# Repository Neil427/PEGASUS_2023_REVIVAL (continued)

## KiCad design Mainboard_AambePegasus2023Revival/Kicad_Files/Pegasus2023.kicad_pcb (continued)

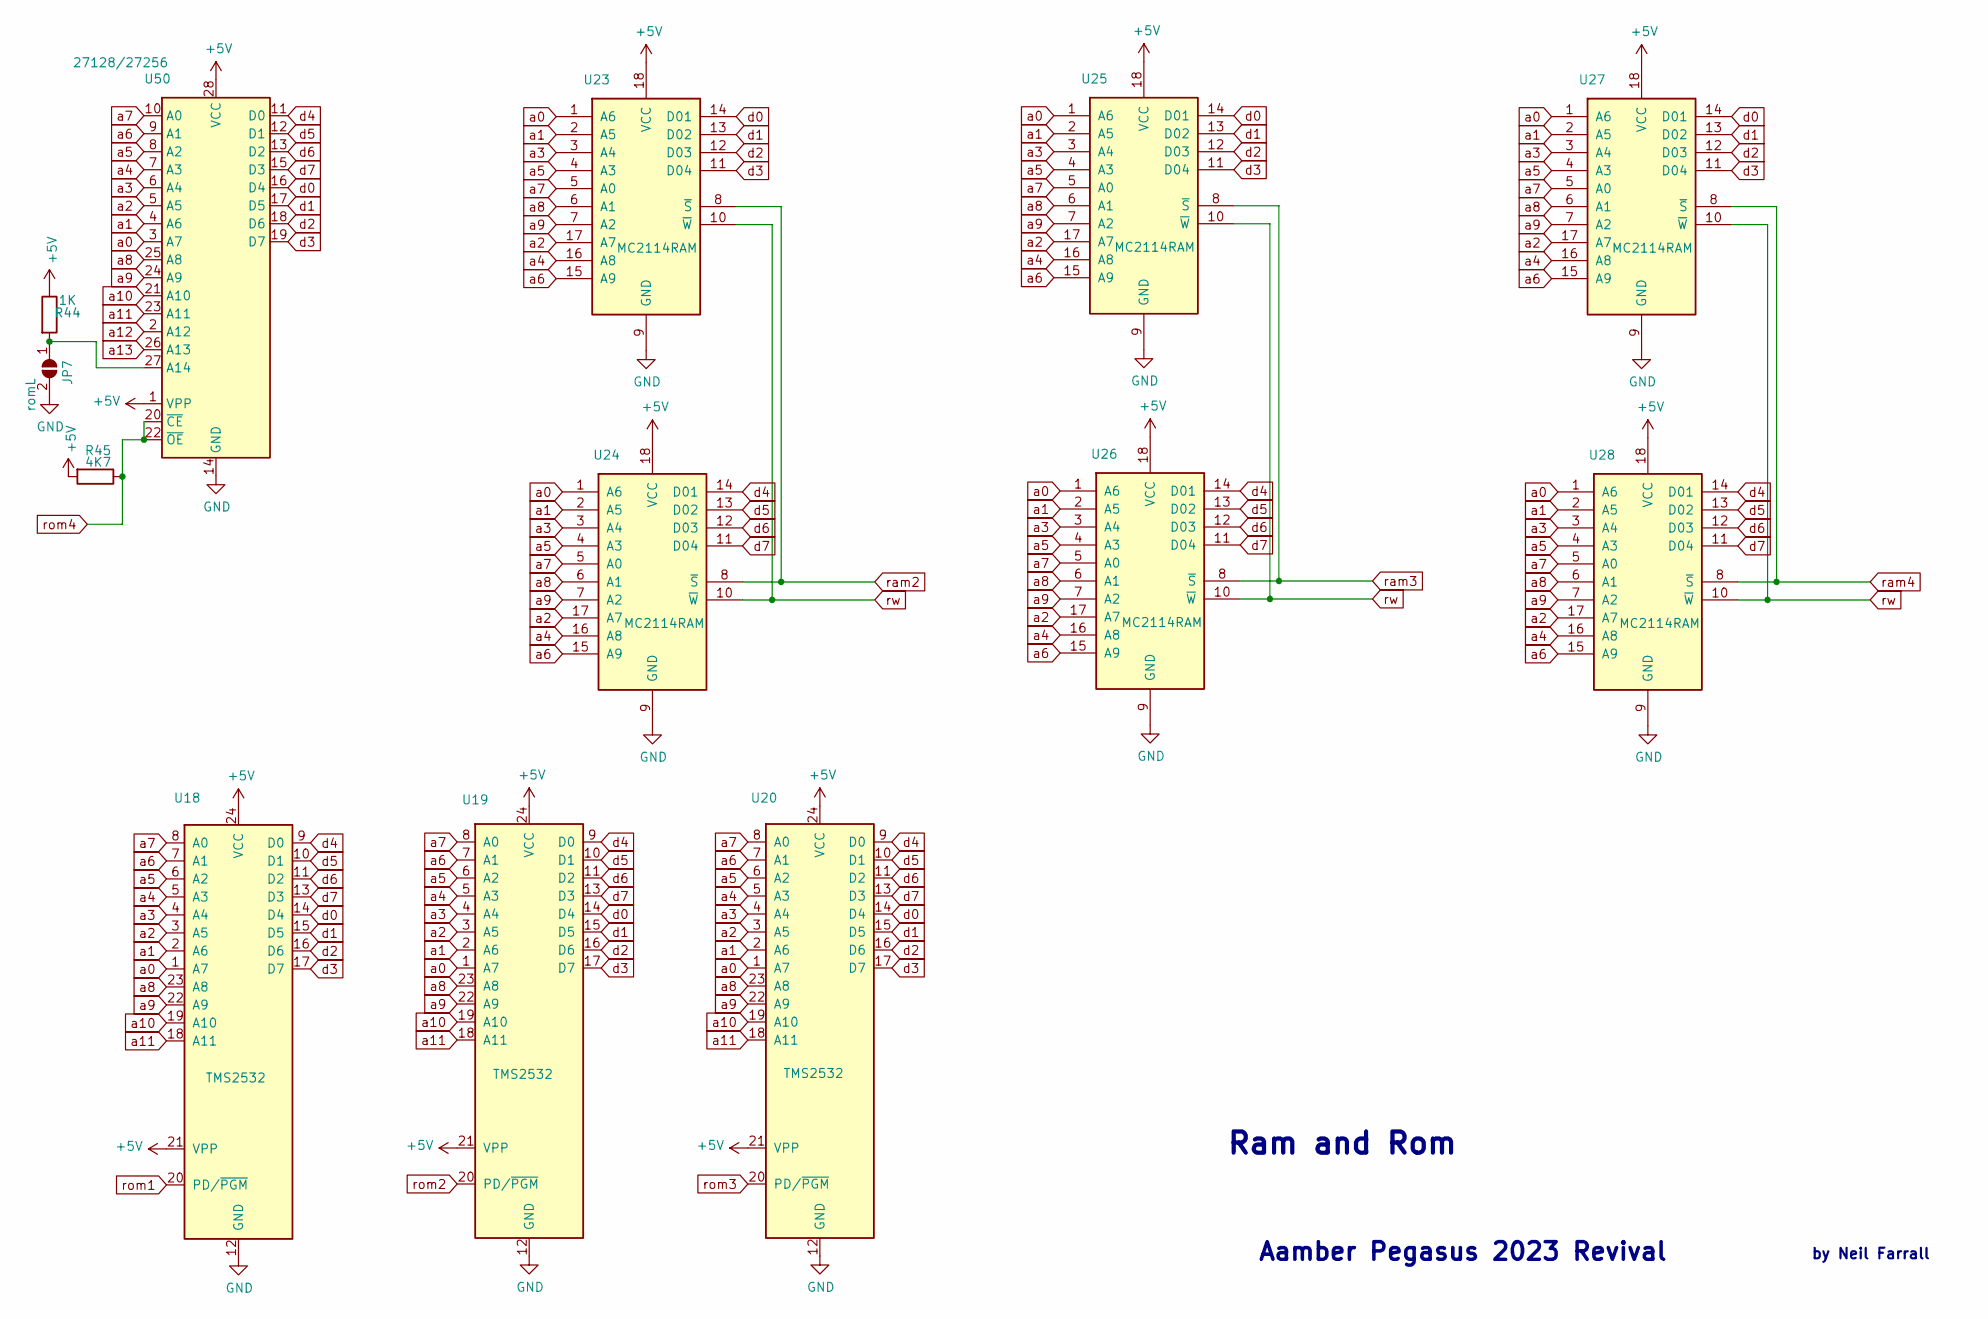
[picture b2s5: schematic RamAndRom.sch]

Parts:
JP7: romL; SolderJumper-2_P1.3mm_Open_Pad1.0x1.5mm
R44: 1K; R_Axial_DIN0411_L9.9mm_D3.6mm_P15.24mm_Horizontal
R45: 4K7; R_Axial_DIN0411_L9.9mm_D3.6mm_P15.24mm_Horizontal
U18, U19, U20: TMS2532; DIP-24_W15.24mm_Socket_LongPads
U23, U24, U25, U26, U27, U28: MC2114RAM; DIP-18_W7.62mm_Socket_LongPads
U50: 27128/27256; DIP-28_W15.24mm

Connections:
unnamed: JP7.1 (A), R44.2, U50.27 (A14)
a0: U18.1 (A7), U19.1 (A7), U20.1 (A7), U23.1 (A6), U24.1 (A6), U25.1 (A6), U26.1 (A6), U27.1 (A6), U28.1 (A6), U50.3 (A7); also elsewhere on the board
a1: U18.2 (A6), U19.2 (A6), U20.2 (A6), U23.2 (A5), U24.2 (A5), U25.2 (A5), U26.2 (A5), U27.2 (A5), U28.2 (A5), U50.4 (A6); also elsewhere on the board
a2: U18.3 (A5), U19.3 (A5), U20.3 (A5), U23.17 (A7), U24.17 (A7), U25.17 (A7), U26.17 (A7), U27.17 (A7), U28.17 (A7), U50.5 (A5); also elsewhere on the board
a3: U18.4 (A4), U19.4 (A4), U20.4 (A4), U23.3 (A4), U24.3 (A4), U25.3 (A4), U26.3 (A4), U27.3 (A4), U28.3 (A4), U50.6 (A4); also elsewhere on the board
a4: U18.5 (A3), U19.5 (A3), U20.5 (A3), U23.16 (A8), U24.16 (A8), U25.16 (A8), U26.16 (A8), U27.16 (A8), U28.16 (A8), U50.7 (A3); also elsewhere on the board
a5: U18.6 (A2), U19.6 (A2), U20.6 (A2), U23.4 (A3), U24.4 (A3), U25.4 (A3), U26.4 (A3), U27.4 (A3), U28.4 (A3), U50.8 (A2); also elsewhere on the board
a6: U18.7 (A1), U19.7 (A1), U20.7 (A1), U23.15 (A9), U24.15 (A9), U25.15 (A9), U26.15 (A9), U27.15 (A9), U28.15 (A9), U50.9 (A1); also elsewhere on the board
a7: U18.8 (A0), U19.8 (A0), U20.8 (A0), U23.5 (A0), U24.5 (A0), U25.5 (A0), U26.5 (A0), U27.5 (A0), U28.5 (A0), U50.10 (A0); also elsewhere on the board
a8: U18.23 (A8), U19.23 (A8), U20.23 (A8), U23.6 (A1), U24.6 (A1), U25.6 (A1), U26.6 (A1), U27.6 (A1), U28.6 (A1), U50.25 (A8); also elsewhere on the board
a9: U18.22 (A9), U19.22 (A9), U20.22 (A9), U23.7 (A2), U24.7 (A2), U25.7 (A2), U26.7 (A2), U27.7 (A2), U28.7 (A2), U50.24 (A9); also elsewhere on the board
a10: U18.19 (A10), U19.19 (A10), U20.19 (A10), U50.21 (A10); also elsewhere on the board
a11: U18.18 (A11), U19.18 (A11), U20.18 (A11), U50.23 (A11); also elsewhere on the board
a12: U50.2 (A12); also elsewhere on the board
a13: U50.26 (A13); also elsewhere on the board
d0: U18.14 (D4), U19.14 (D4), U20.14 (D4), U23.14 (D01), U25.14 (D01), U27.14 (D01), U50.16 (D4); also elsewhere on the board
d1: U18.15 (D5), U19.15 (D5), U20.15 (D5), U23.13 (D02), U25.13 (D02), U27.13 (D02), U50.17 (D5); also elsewhere on the board
d2: U18.16 (D6), U19.16 (D6), U20.16 (D6), U23.12 (D03), U25.12 (D03), U27.12 (D03), U50.18 (D6); also elsewhere on the board
d3: U18.17 (D7), U19.17 (D7), U20.17 (D7), U23.11 (D04), U25.11 (D04), U27.11 (D04), U50.19 (D7); also elsewhere on the board
d4: U18.9 (D0), U19.9 (D0), U20.9 (D0), U24.14 (D01), U26.14 (D01), U28.14 (D01), U50.11 (D0); also elsewhere on the board
d5: U18.10 (D1), U19.10 (D1), U20.10 (D1), U24.13 (D02), U26.13 (D02), U28.13 (D02), U50.12 (D1); also elsewhere on the board
d6: U18.11 (D2), U19.11 (D2), U20.11 (D2), U24.12 (D03), U26.12 (D03), U28.12 (D03), U50.13 (D2); also elsewhere on the board
d7: U18.13 (D3), U19.13 (D3), U20.13 (D3), U24.11 (D04), U26.11 (D04), U28.11 (D04), U50.15 (D3); also elsewhere on the board
ram2: U23.8 (~S), U24.8 (~S); also elsewhere on the board
ram3: U25.8 (~S), U26.8 (~S); also elsewhere on the board
ram4: U27.8 (~S), U28.8 (~S); also elsewhere on the board
rom1: U18.20 (PD/~PGM); also elsewhere on the board
rom2: U19.20 (PD/~PGM); also elsewhere on the board
rom3: U20.20 (PD/~PGM); also elsewhere on the board
rom4: R45.1, U50.20 (~CE), U50.22 (~OE); also elsewhere on the board
rw: U23.10 (~W), U24.10 (~W), U25.10 (~W), U26.10 (~W), U27.10 (~W), U28.10 (~W); also elsewhere on the board

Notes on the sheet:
Aamber Pegasus 2023 Revival
by Neil Farrall
Ram and Rom

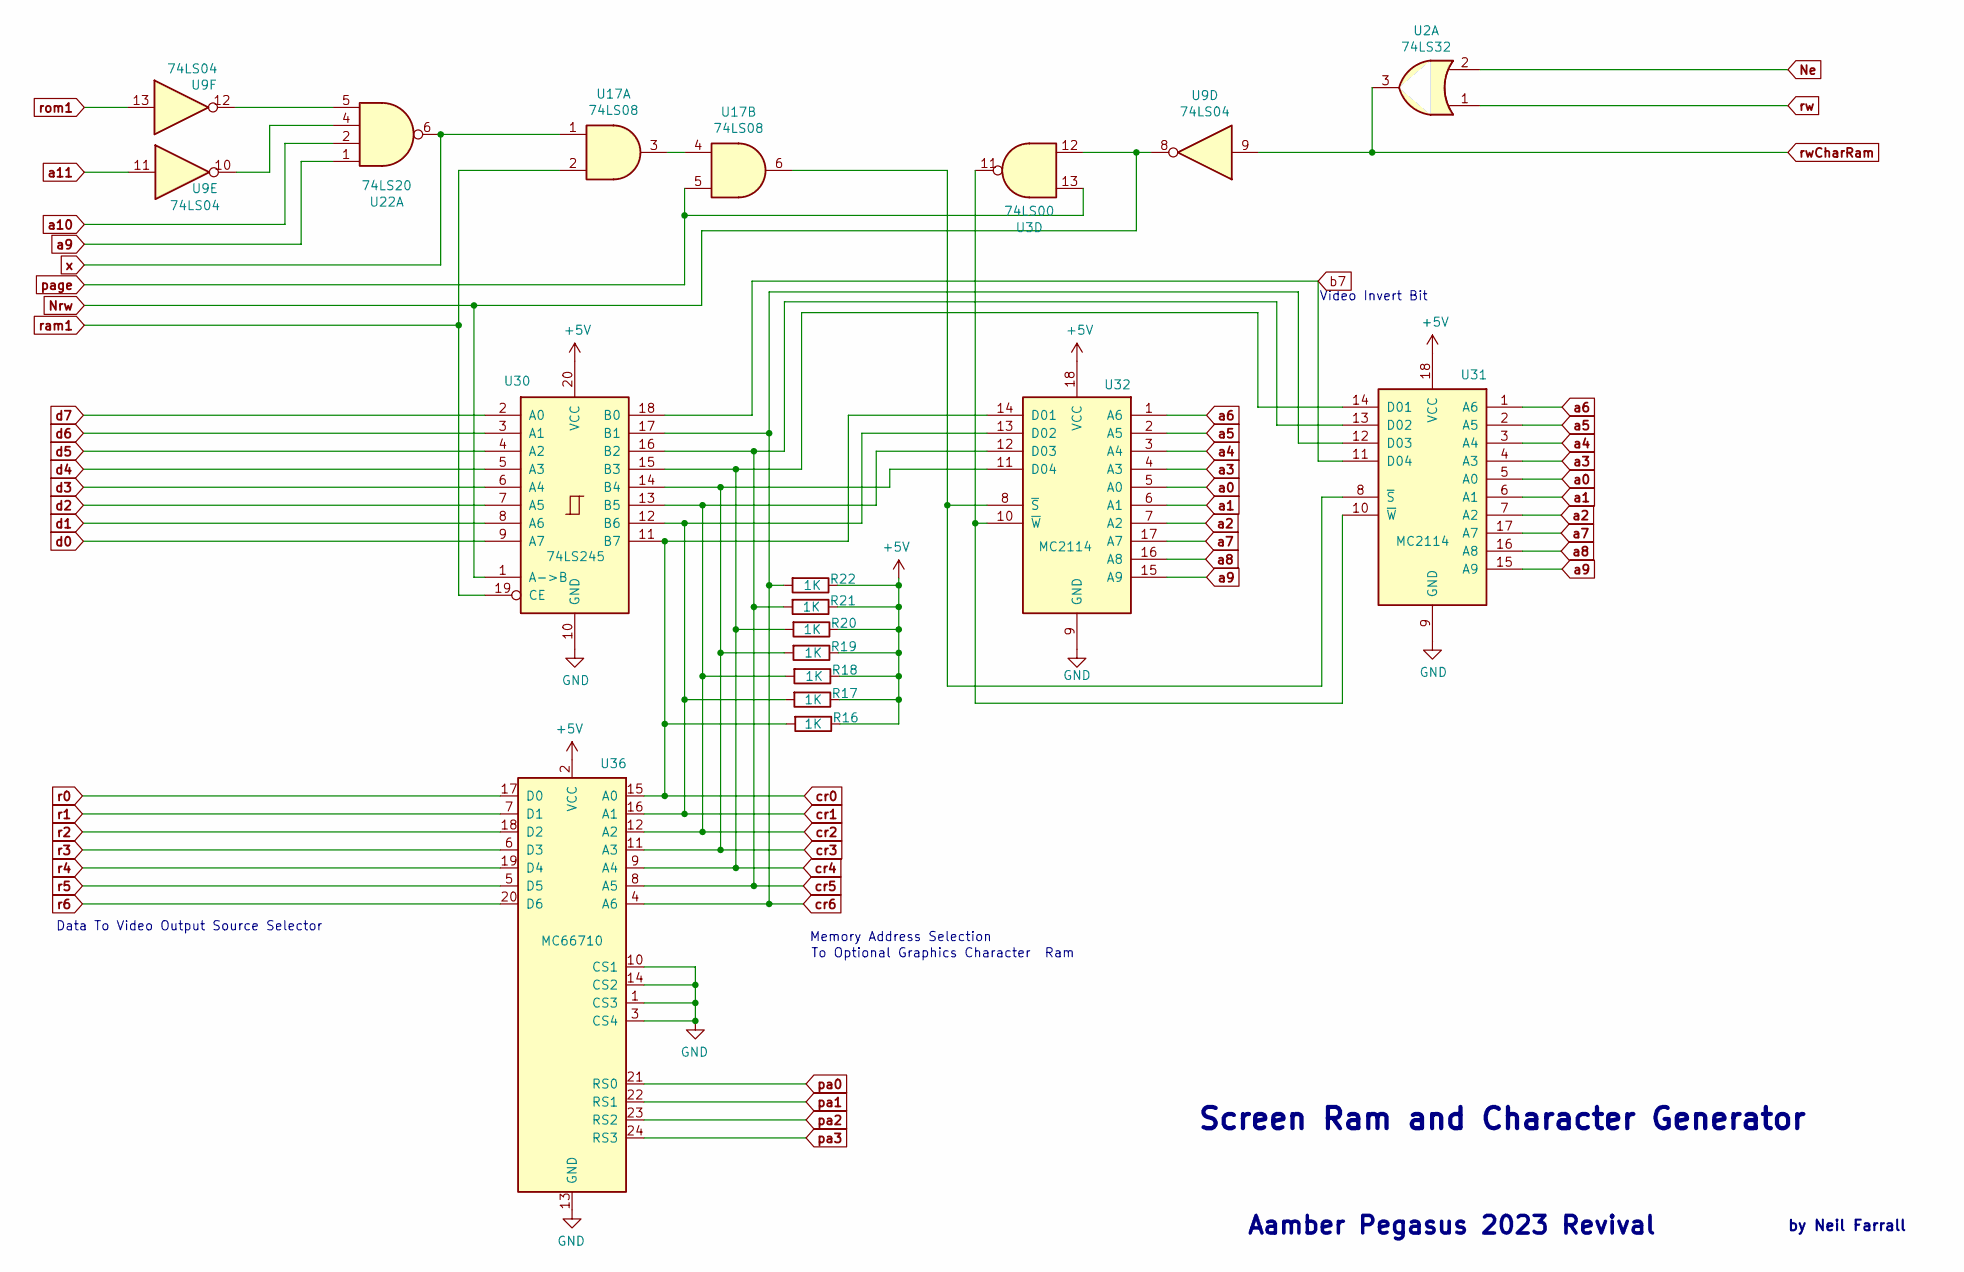
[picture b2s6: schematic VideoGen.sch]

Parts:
R16, R17, R18, R19, R20, R21, R22: 1K; R_Axial_DIN0411_L9.9mm_D3.6mm_P15.24mm_Horizontal
U2: 74LS32; DIP-14_W7.62mm_Socket_LongPads
U3: 74LS00; DIP-14_W7.62mm_Socket_LongPads
U9: 74LS04; DIP-14_W7.62mm_Socket_LongPads
U17: 74LS08; DIP-14_W7.62mm_Socket_LongPads
U22: 74LS20; DIP-14_W7.62mm_Socket_LongPads
U30: 74LS245; DIP-20_W7.62mm_Socket_LongPads
U31, U32: MC2114; DIP-18_W7.62mm_Socket_LongPads
U36: MC66710; DIP-24_W15.24mm_Socket_LongPads

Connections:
Ne: U2.2; also elsewhere on the board
unnamed: U3.11, U31.10 (~W), U32.10 (~W)
unnamed: U17.3, U17.4
unnamed: U17.6, U31.8 (~S), U32.8 (~S)
unnamed: U9.10, U22.4
unnamed: U9.12, U22.5
Nrw: U3.12, U9.8, U30.1 (A->B); also elsewhere on the board
a0: U31.5 (A0), U32.5 (A0); also elsewhere on the board
a1: U31.6 (A1), U32.6 (A1); also elsewhere on the board
a2: U31.7 (A2), U32.7 (A2); also elsewhere on the board
a3: U31.4 (A3), U32.4 (A3); also elsewhere on the board
a4: U31.3 (A4), U32.3 (A4); also elsewhere on the board
a5: U31.2 (A5), U32.2 (A5); also elsewhere on the board
a6: U31.1 (A6), U32.1 (A6); also elsewhere on the board
a7: U31.17 (A7), U32.17 (A7); also elsewhere on the board
a8: U31.16 (A8), U32.16 (A8); also elsewhere on the board
a9: U22.1, U31.15 (A9), U32.15 (A9); also elsewhere on the board
a10: U22.2; also elsewhere on the board
a11: U9.11; also elsewhere on the board
b7: U30.18 (B0), U31.11 (D04); also elsewhere on the board
cr0: R16.2, U30.11 (B7), U32.14 (D01), U36.15 (A0); also elsewhere on the board
cr1: R17.2, U30.12 (B6), U32.13 (D02), U36.16 (A1); also elsewhere on the board
cr2: R18.2, U30.13 (B5), U32.12 (D03), U36.12 (A2); also elsewhere on the board
cr3: R19.2, U30.14 (B4), U32.11 (D04), U36.11 (A3); also elsewhere on the board
cr4: R20.2, U30.15 (B3), U31.14 (D01), U36.9 (A4); also elsewhere on the board
cr5: R21.2, U30.16 (B2), U31.13 (D02), U36.8 (A5); also elsewhere on the board
cr6: R22.2, U30.17 (B1), U31.12 (D03), U36.4 (A6); also elsewhere on the board
d0: U30.9 (A7); also elsewhere on the board
d1: U30.8 (A6); also elsewhere on the board
d2: U30.7 (A5); also elsewhere on the board
d3: U30.6 (A4); also elsewhere on the board
d4: U30.5 (A3); also elsewhere on the board
d5: U30.4 (A2); also elsewhere on the board
d6: U30.3 (A1); also elsewhere on the board
d7: U30.2 (A0); also elsewhere on the board
pa0: U36.21 (RS0); also elsewhere on the board
pa1: U36.22 (RS1); also elsewhere on the board
pa2: U36.23 (RS2); also elsewhere on the board
pa3: U36.24 (RS3); also elsewhere on the board
page: U3.13, U17.5; also elsewhere on the board
r0: U36.17 (D0); also elsewhere on the board
r1: U36.7 (D1); also elsewhere on the board
r2: U36.18 (D2); also elsewhere on the board
r3: U36.6 (D3); also elsewhere on the board
r4: U36.19 (D4); also elsewhere on the board
r5: U36.5 (D5); also elsewhere on the board
r6: U36.20 (D6); also elsewhere on the board
ram1: U17.2, U30.19 (CE); also elsewhere on the board
rom1: U9.13; also elsewhere on the board
rw: U2.1; also elsewhere on the board
rwCharRam: U2.3, U9.9; also elsewhere on the board
x: U17.1, U22.6; also elsewhere on the board

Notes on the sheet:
Aamber Pegasus 2023 Revival
by Neil Farrall
Screen Ram and Character Generator
Memory Address Selection
Data To Video Output Source Selector
To Optional Graphics Character Ram
Video Invert Bit

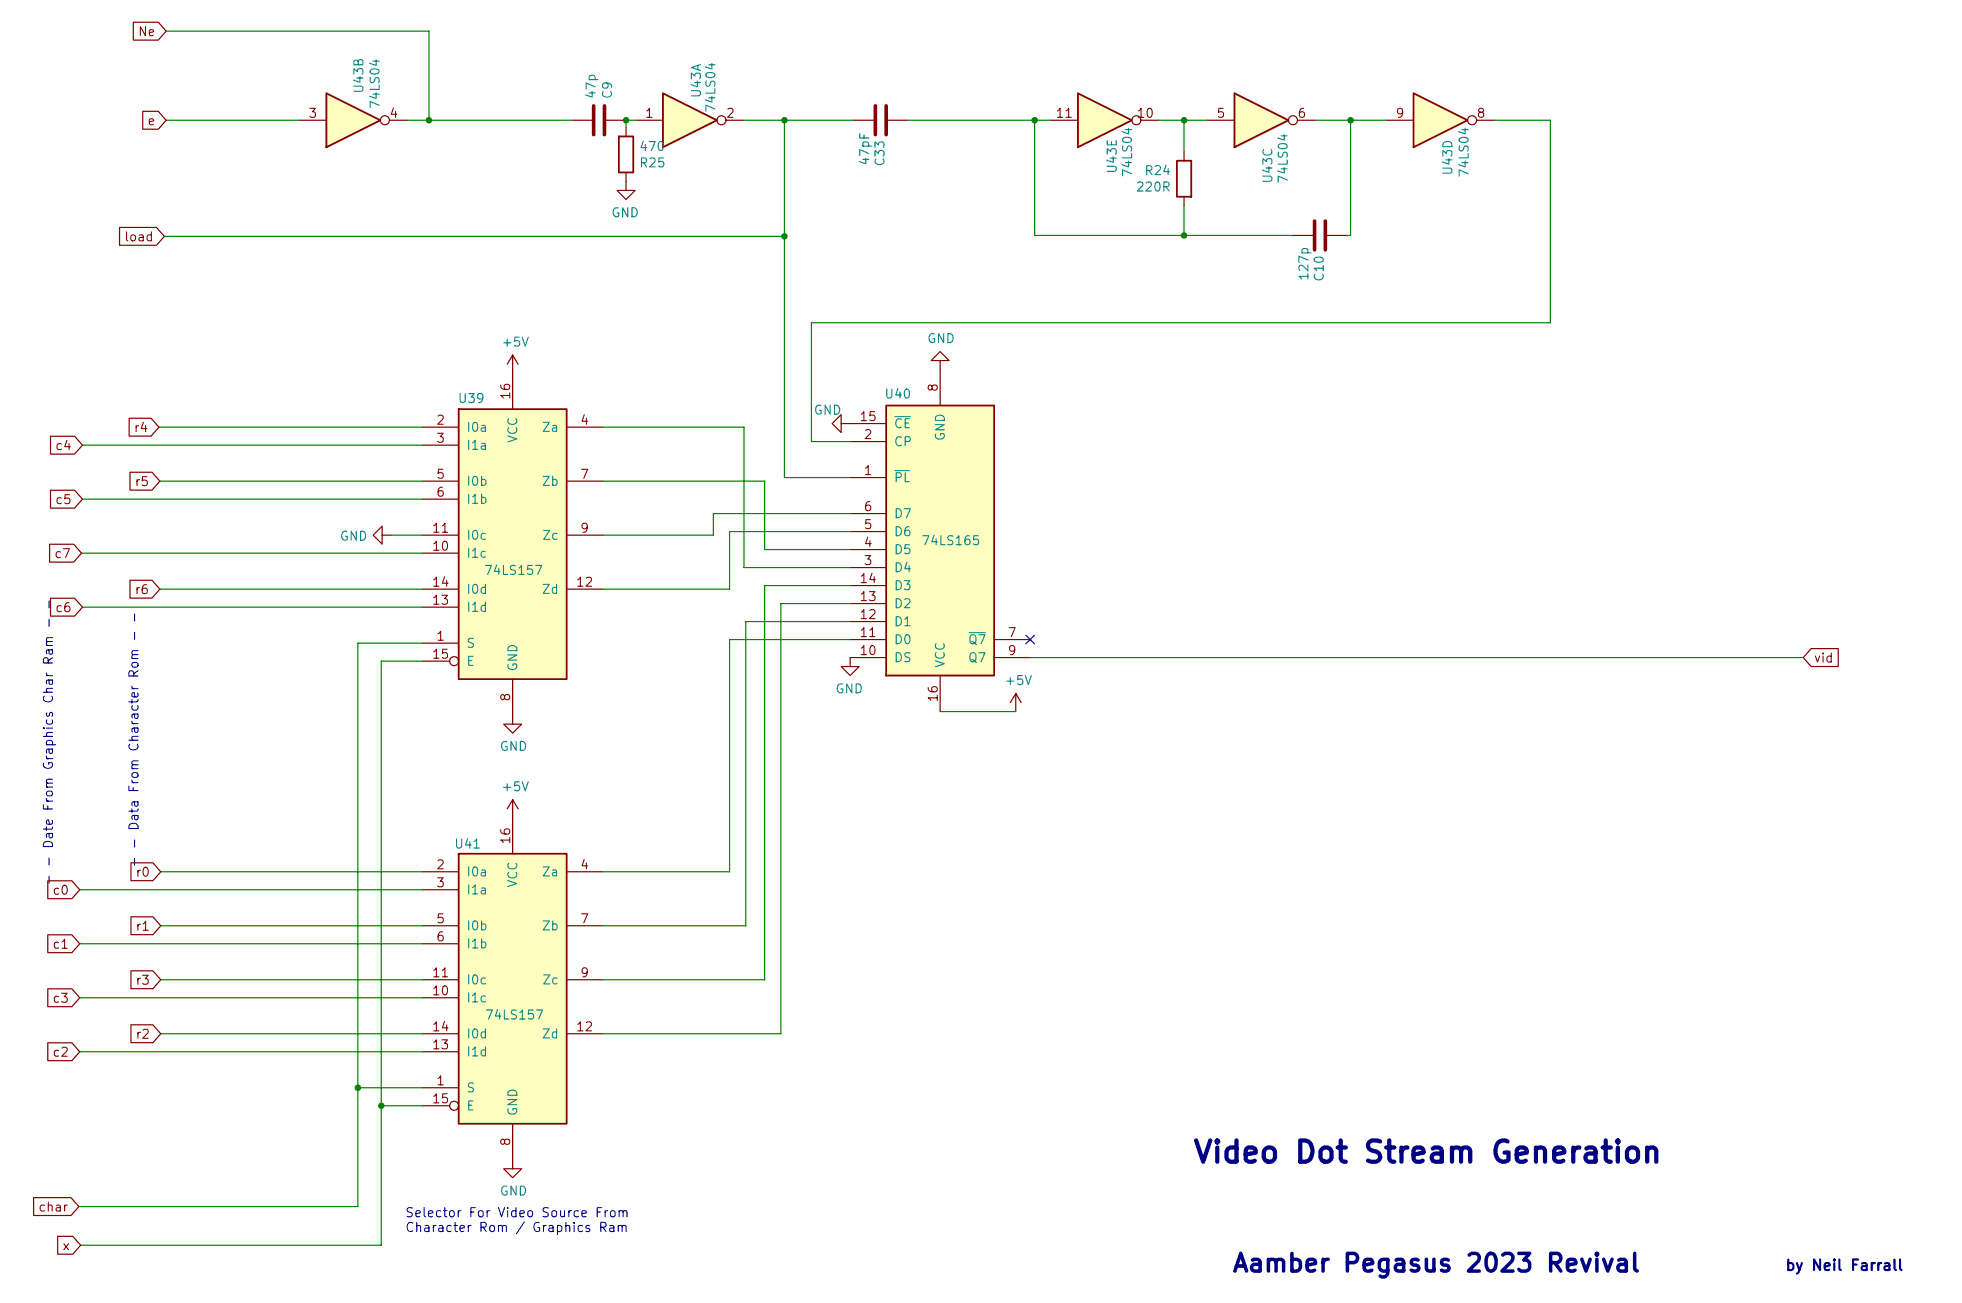
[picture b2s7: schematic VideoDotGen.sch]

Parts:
C9: 47p; C_Disc_D3.8mm_W2.6mm_P2.50mm
C10: 127p; C_Disc_D3.8mm_W2.6mm_P2.50mm
C33: 47pF; C_Disc_D3.8mm_W2.6mm_P2.50mm
R24: 220R; R_Axial_DIN0411_L9.9mm_D3.6mm_P15.24mm_Horizontal
R25: 470; R_Axial_DIN0411_L9.9mm_D3.6mm_P15.24mm_Horizontal
U39, U41: 74LS157; DIP-16_W7.62mm_Socket_LongPads
U40: 74LS165; DIP-16_W7.62mm_Socket_LongPads
U43: 74LS04; DIP-14_W7.62mm_Socket_LongPads

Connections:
Ne: C9.2, U43.4; also elsewhere on the board
unnamed: C9.1, R25.2, U43.1
unnamed: C10.1, U43.6, U43.9
unnamed: C10.2, C33.1, R24.2, U43.11
unnamed: R24.1, U43.5, U43.10
unnamed: U39.4 (Za), U40.3 (D4)
unnamed: U39.7 (Zb), U40.4 (D5)
unnamed: U39.9 (Zc), U40.6 (D7)
unnamed: U39.12 (Zd), U40.5 (D6)
unnamed: U40.2 (CP), U43.8
unnamed: U40.11 (D0), U41.4 (Za)
unnamed: U40.12 (D1), U41.7 (Zb)
unnamed: U40.13 (D2), U41.12 (Zd)
unnamed: U40.14 (D3), U41.9 (Zc)
c0: U41.3 (I1a); also elsewhere on the board
c1: U41.6 (I1b); also elsewhere on the board
c2: U41.13 (I1d); also elsewhere on the board
c3: U41.10 (I1c); also elsewhere on the board
c4: U39.3 (I1a); also elsewhere on the board
c5: U39.6 (I1b); also elsewhere on the board
c6: U39.13 (I1d); also elsewhere on the board
c7: U39.10 (I1c); also elsewhere on the board
char: U39.1 (S), U41.1 (S); also elsewhere on the board
e: U43.3; also elsewhere on the board
load: C33.2, U40.1 (~PL), U43.2; also elsewhere on the board
r0: U41.2 (I0a); also elsewhere on the board
r1: U41.5 (I0b); also elsewhere on the board
r2: U41.14 (I0d); also elsewhere on the board
r3: U41.11 (I0c); also elsewhere on the board
r4: U39.2 (I0a); also elsewhere on the board
r5: U39.5 (I0b); also elsewhere on the board
r6: U39.14 (I0d); also elsewhere on the board
vid: U40.9 (Q7); also elsewhere on the board
x: U39.15 (E), U41.15 (E); also elsewhere on the board

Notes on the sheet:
Aamber Pegasus 2023 Revival
by Neil Farrall
Video Dot Stream Generation
Selector For Video Source From Character Rom / Graphics Ram
- - Date From Graphics Char Ram - -
- - Data From Character Rom - -

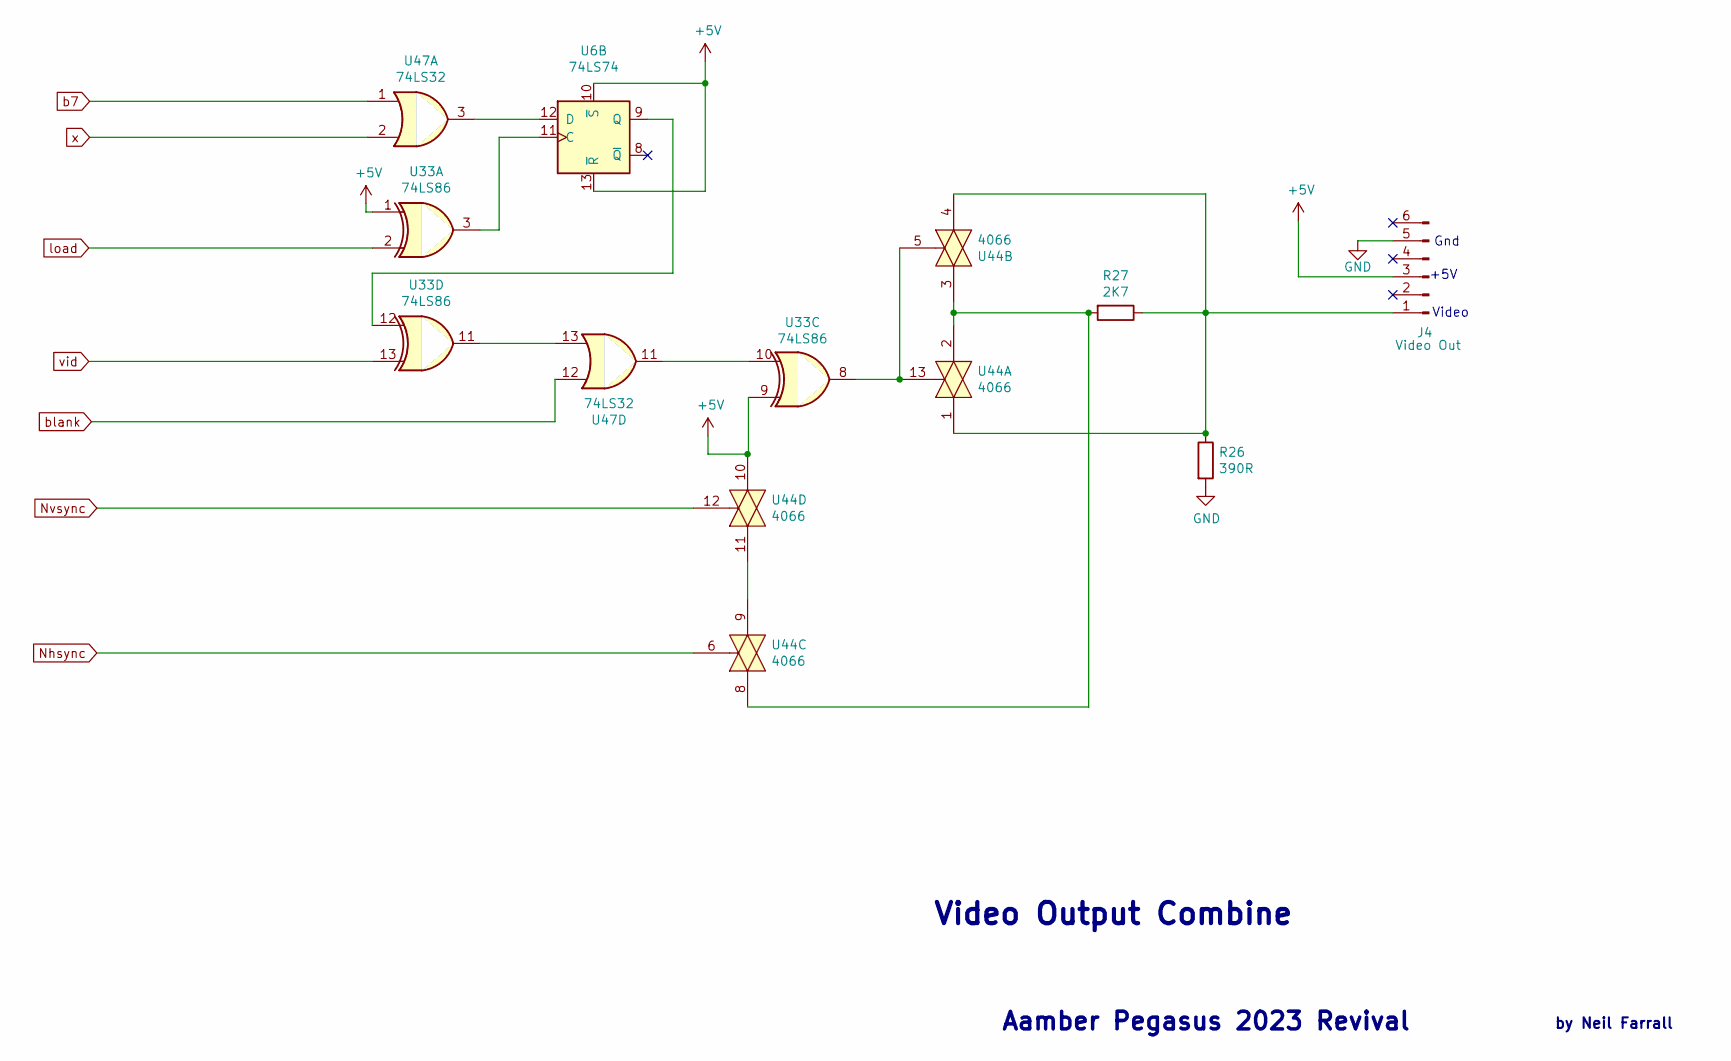
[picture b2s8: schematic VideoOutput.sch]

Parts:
J4: Video Out; PinHeader_1x06_P2.54mm_Horizontal
R26: 390R; R_Axial_DIN0411_L9.9mm_D3.6mm_P15.24mm_Horizontal
R27: 2K7; R_Axial_DIN0411_L9.9mm_D3.6mm_P15.24mm_Horizontal
U6: 74LS74; DIP-14_W7.62mm_Socket_LongPads
U33: 74LS86; DIP-14_W7.62mm_Socket_LongPads
U44: 4066; DIP-14_W7.62mm_Socket_LongPads
U47: 74LS32; DIP-14_W7.62mm_Socket_LongPads

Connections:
unnamed: J4.1, R26.1, R27.1, U44.1, U44.4
unnamed: R27.2, U44.2, U44.3, U44.8
unnamed: U6.11 (C), U33.3
unnamed: U33.8, U44.5, U44.13
unnamed: U33.10, U47.11
unnamed: U33.11, U47.13
unnamed: U6.9 (Q), U33.12
unnamed: U44.9, U44.11
unnamed: U6.12 (D), U47.3
Nhsync: U44.6; also elsewhere on the board
Nvsync: U44.12; also elsewhere on the board
b7: U47.1; also elsewhere on the board
blank: U47.12; also elsewhere on the board
load: U33.2; also elsewhere on the board
vid: U33.13; also elsewhere on the board
x: U47.2; also elsewhere on the board

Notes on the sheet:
Aamber Pegasus 2023 Revival
by Neil Farrall
Video Output Combine
Gnd
+5V
Video

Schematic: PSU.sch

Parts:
C11: 1uF 35V T; CP_Radial_Tantal_D5.0mm_P2.50mm
C12, C13, C14, C15, C16, C17, C18, C19, C20, C21, C22, C23, C24, C25, C26, C27, C28, C29, C30, C31, C103: 100N; C_Disc_D11.0mm_W5.0mm_P5.00mm
C34: 47uF; CP_Radial_Tantal_D8.0mm_P5.00mm
D2: GreenLED; LED_D5.0mm
J5: Power; PhoenixContact_MC_1,5_4-G-5.08_1x04_P5.08mm_Horizontal
R1, R2: 100R; R_Axial_DIN0411_L9.9mm_D3.6mm_P15.24mm_Horizontal
U1: 74LS14; DIP-14_W7.62mm_Socket_LongPads
U2, U47: 74LS32; DIP-14_W7.62mm_Socket_LongPads
U3: 74LS00; DIP-14_W7.62mm_Socket_LongPads
U4: 74LS21; DIP-14_W7.62mm_Socket_LongPads
U5: 74LS123; DIP-16_W7.62mm_Socket_LongPads
U6, U46: 74LS74; DIP-14_W7.62mm_Socket_LongPads
U9, U43: 74LS04; DIP-14_W7.62mm_Socket_LongPads
U14, U15, U16: 74LS139; DIP-16_W7.62mm_Socket_LongPads
U17: 74LS08; DIP-14_W7.62mm_Socket_LongPads
U22, U49: 74LS20; DIP-14_W7.62mm_Socket_LongPads
U33: 74LS86; DIP-14_W7.62mm_Socket_LongPads
U44: 4066; DIP-14_W7.62mm_Socket_LongPads
Ureg1: LM309K; TO-3; MPN LM7805CT; Digi-Key_PN LM7805CT-ND

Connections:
unnamed: C34.1, J5.2, Ureg1.2 (VI)
unnamed: D2.1 (K), R1.1
unnamed: D2.2 (A), R2.2

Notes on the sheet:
Aamber Pegasus 2023 Revival
by Neil Farrall
Power Supply
POWER

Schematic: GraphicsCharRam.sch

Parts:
U2: 74LS32; DIP-14_W7.62mm_Socket_LongPads
U33: 74LS86; DIP-14_W7.62mm_Socket_LongPads
U34, U35, U37, U38: MC2114; DIP-18_W7.62mm_Socket_LongPads
U42: 74LS245; DIP-20_W7.62mm_Socket_LongPads

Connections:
unnamed: U2.6, U34.10 (~W), U35.10 (~W), U37.10 (~W), U38.10 (~W)
unnamed: U33.6, U35.8 (~S), U38.8 (~S)
Nrw: U42.1 (A->B); also elsewhere on the board
c0: U37.14 (D01), U38.14 (D01), U42.11 (B7); also elsewhere on the board
c1: U37.13 (D02), U38.13 (D02), U42.12 (B6); also elsewhere on the board
c2: U37.12 (D03), U38.12 (D03), U42.13 (B5); also elsewhere on the board
c3: U37.11 (D04), U38.11 (D04), U42.14 (B4); also elsewhere on the board
c4: U34.14 (D01), U35.14 (D01), U42.15 (B3); also elsewhere on the board
c5: U34.13 (D02), U35.13 (D02), U42.16 (B2); also elsewhere on the board
c6: U34.12 (D03), U35.12 (D03), U42.17 (B1); also elsewhere on the board
c7: U34.11 (D04), U35.11 (D04), U42.18 (B0); also elsewhere on the board
charram: U2.4, U42.19 (CE); also elsewhere on the board
cr0: U34.15 (A9), U35.15 (A9), U37.15 (A9), U38.15 (A9); also elsewhere on the board
cr1: U34.7 (A2), U35.7 (A2), U37.7 (A2), U38.7 (A2); also elsewhere on the board
cr2: U34.6 (A1), U35.6 (A1), U37.6 (A1), U38.6 (A1); also elsewhere on the board
cr3: U34.5 (A0), U35.5 (A0), U37.5 (A0), U38.5 (A0); also elsewhere on the board
cr4: U34.4 (A3), U35.4 (A3), U37.4 (A3), U38.4 (A3); also elsewhere on the board
cr5: U34.3 (A4), U35.3 (A4), U37.3 (A4), U38.3 (A4); also elsewhere on the board
cr6: U33.4, U34.8 (~S), U37.8 (~S); also elsewhere on the board
d0: U42.9 (A7); also elsewhere on the board
d1: U42.8 (A6); also elsewhere on the board
d2: U42.7 (A5); also elsewhere on the board
d3: U42.6 (A4); also elsewhere on the board
d4: U42.5 (A3); also elsewhere on the board
d5: U42.4 (A2); also elsewhere on the board
d6: U42.3 (A1); also elsewhere on the board
d7: U42.2 (A0); also elsewhere on the board
pa0: U34.2 (A5), U35.2 (A5), U37.2 (A5), U38.2 (A5); also elsewhere on the board
pa1: U34.1 (A6), U35.1 (A6), U37.1 (A6), U38.1 (A6); also elsewhere on the board
pa2: U34.17 (A7), U35.17 (A7), U37.17 (A7), U38.17 (A7); also elsewhere on the board
pa3: U34.16 (A8), U35.16 (A8), U37.16 (A8), U38.16 (A8); also elsewhere on the board
rwCharRam: U2.5; also elsewhere on the board

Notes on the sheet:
opt.
Optional Graphics Character Ram
Aamber Pegasus 2023 Revival
1.0
by Neil Farrall
Character Address Selection
Graphics Char Data To Video Output Source Selector

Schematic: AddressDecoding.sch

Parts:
JP1: rom2; SolderJumper-2_P1.3mm_Open_Pad1.0x1.5mm
JP2: rom3; SolderJumper-2_P1.3mm_Open_Pad1.0x1.5mm
JP3: rom2 alt; SolderJumper-2_P1.3mm_Open_Pad1.0x1.5mm
JP4: rom3 alt; SolderJumper-2_P1.3mm_Open_Pad1.0x1.5mm
JP5, JP8: opt.; SolderJumper-2_P1.3mm_Open_Pad1.0x1.5mm
R13: 1K; R_Axial_DIN0411_L9.9mm_D3.6mm_P15.24mm_Horizontal
U2: 74LS32; DIP-14_W7.62mm_Socket_LongPads
U3: 74LS00; DIP-14_W7.62mm_Socket_LongPads
U4: 74LS21; DIP-14_W7.62mm_Socket_LongPads
U9: 74LS04; DIP-14_W7.62mm_Socket_LongPads
U14, U15, U16: 74LS139; DIP-16_W7.62mm_Socket_LongPads
U17: 74LS08; DIP-14_W7.62mm_Socket_LongPads

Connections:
unnamed: JP1.1 (A), U16.11 (O1)
unnamed: JP2.1 (A), U16.12 (O0)
unnamed: JP3.2 (B), U15.5 (O1)
unnamed: JP4.2 (B), U15.4 (O0)
unnamed: JP5.1 (A), JP8.1 (A), U16.4 (O0), U16.15 (E)
unnamed: JP5.2 (B), R13.2, U17.13
unnamed: U3.2, U9.2
unnamed: U2.11, U14.1 (E)
unnamed: U14.15 (E), U15.9 (O3)
unnamed: U15.1 (E), U16.7 (O3)
unnamed: U2.13, U9.1, U15.6 (O2)
unnamed: U4.12, U15.10 (O2)
unnamed: U4.10, U15.11 (O1)
unnamed: U4.9, U15.12 (O0)
unnamed: U15.15 (E), U16.6 (O2)
unnamed: U4.13, U16.5 (O1)
unnamed: U3.3, U17.9
unnamed: U17.10, U17.11
unnamed: U4.8, U17.12
Nsel: U17.8; also elsewhere on the board
a9: U14.2 (A0); also elsewhere on the board
a10: U14.3 (A1), U14.14 (A0); also elsewhere on the board
a11: U2.12, U3.1, U14.13 (A1); also elsewhere on the board
a12: U15.2 (A0), U15.14 (A0), U16.14 (A0); also elsewhere on the board
a13: U15.3 (A1), U15.13 (A1), U16.13 (A1); also elsewhere on the board
a14: U16.2 (A0); also elsewhere on the board
a15: U16.3 (A1); also elsewhere on the board
charram: U14.5 (O1); also elsewhere on the board
pia1: U14.7 (O3); also elsewhere on the board
pia2: U14.6 (O2); also elsewhere on the board
ram1: U14.9 (O3); also elsewhere on the board
ram2: U14.10 (O2); also elsewhere on the board
ram3: U14.11 (O1); also elsewhere on the board
ram4: U14.12 (O0); also elsewhere on the board
rom1: U15.7 (O3); also elsewhere on the board
rom2: JP1.2 (B), JP3.1 (A); also elsewhere on the board
rom3: JP2.2 (B), JP4.1 (A); also elsewhere on the board
rom4: JP8.2 (B); also elsewhere on the board

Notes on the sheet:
0000 - 3FFF
4000-7FFF
8000-BFFF
C000-FFFF
C000-CFFF
D000-DFFF
F000-FFFF
8000-8FFF
9000-9FFF
A000-AFFF
B000-BFFF
0000-0FFF
1000-1FFF
2000-2FFF
3000-3FFF
E000-EFFF
E000-E7FF
E000-E1FF
E200-E3FF
E400-E5FF
E600-E7FF
(Ram Expansion)
8000-AFFF
4000-AFFF
E800-EFFF
Reserved
B000-B3FF
B400-B7FF
B800-BBFF
BC00-BFFF
Optional D27128 16Kx8 Eprom
Select For Off Board Devices
(Break JP1,2,5 Make JP8,3,4)
- Move Rom address space 0000-3FFF to I/O bus by: Break JP8 and Make JP5
NSEL will then map the following to the external bus: 0000-3FFF - 16K Rom expansion 4000-7FFF - 16K Ram expansion 8000-AFFF - 12K Ram expansion E800-EFFF - 2K I/O expansion
- If using external Rom board, remap Rom2 and 3 to their alternative addresses by: Break JP1,2 and Make JP3,4
Aamber Pegasus 2023 Revival
by Neil Farrall
Address Decoding / Chip Select

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
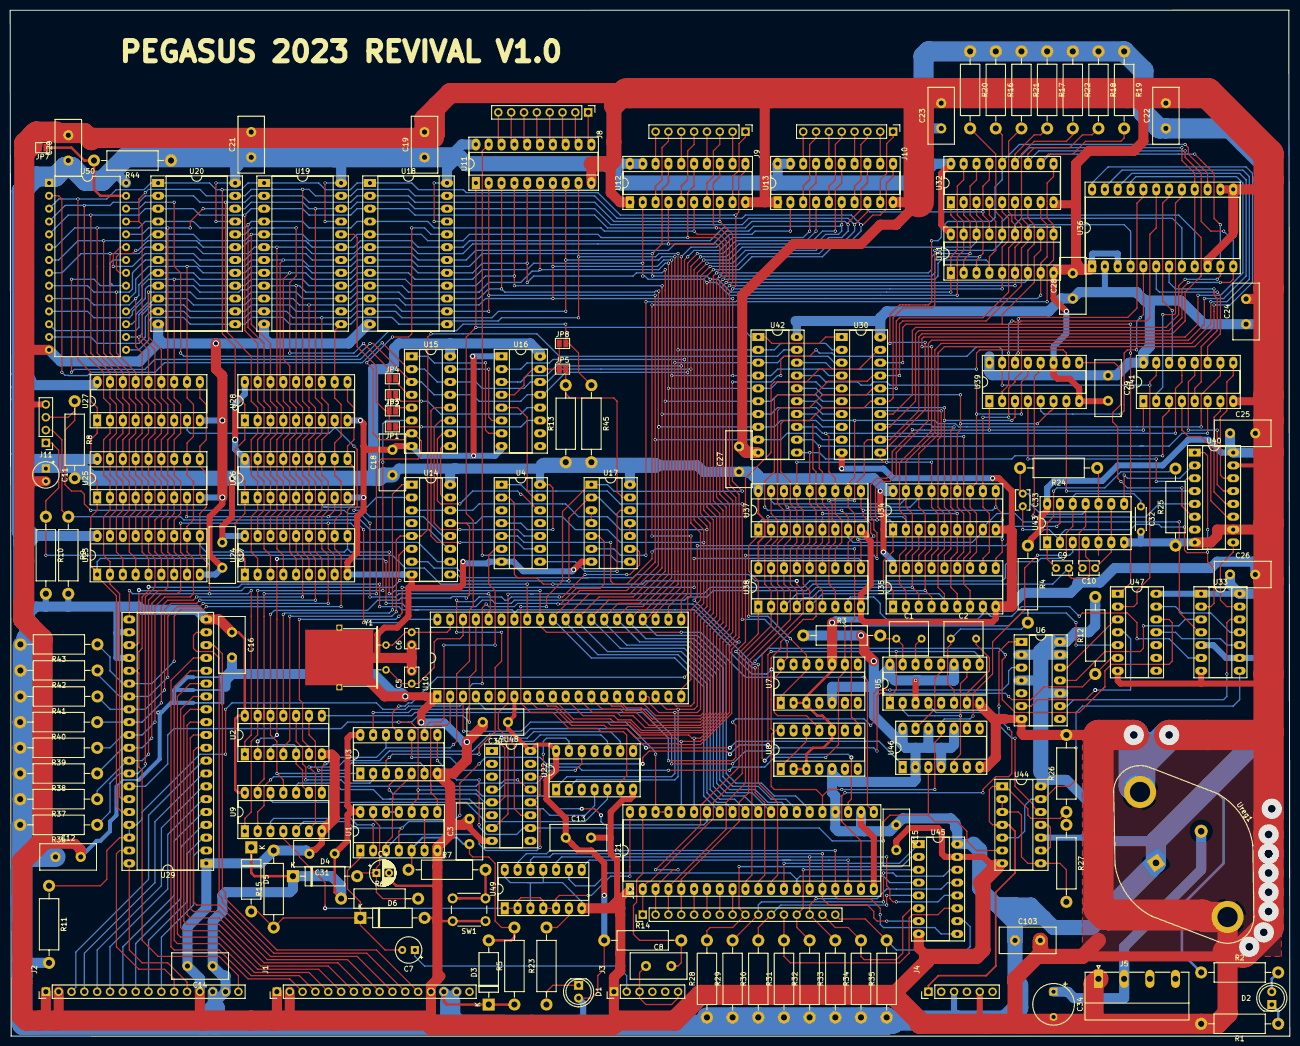
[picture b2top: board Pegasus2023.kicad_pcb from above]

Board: 2 copper layers, 253.2 x 203.0 mm, 156 parts (0 on the bottom side), 239 nets.
